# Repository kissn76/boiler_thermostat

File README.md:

# boiler_thermostat
Boiler theromstat based on ESP32

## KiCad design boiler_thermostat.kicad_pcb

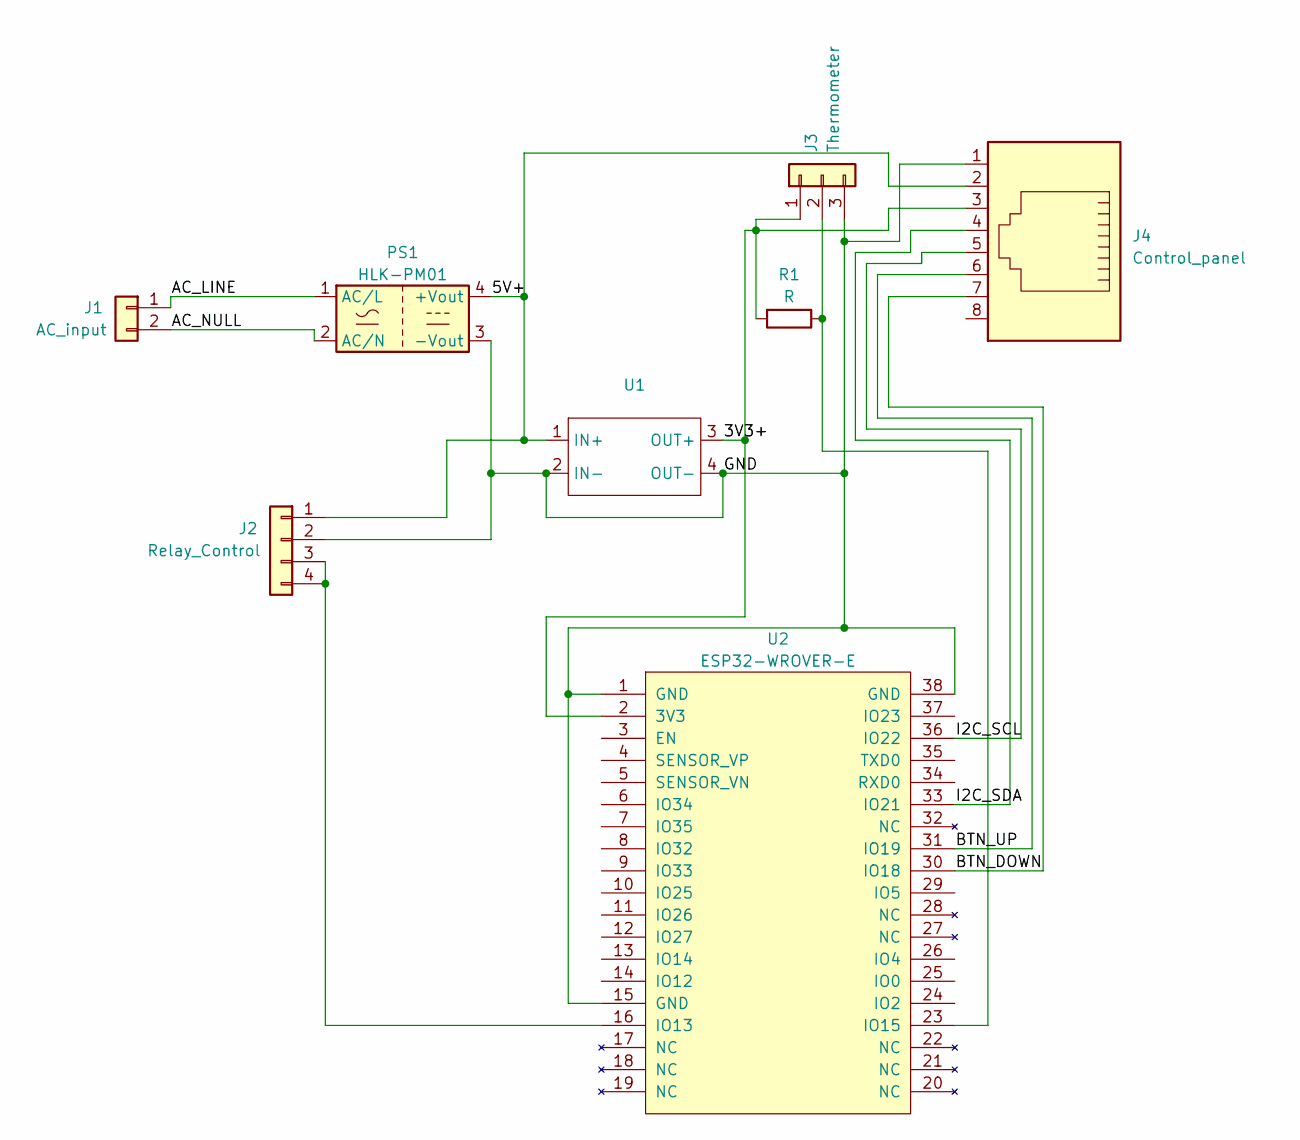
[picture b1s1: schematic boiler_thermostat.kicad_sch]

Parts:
J1: AC_input; Ninigi AC141R-02P-2.54
J2: Relay_Control; TerminalBlock_bornier-4_P5.08mm
J3: Thermometer; TerminalBlock_bornier-3_P5.08mm
J4: Control_panel; RJ45_Keystone_942
PS1: HLK-PM01; Converter_ACDC_HiLink_HLK-PMxx
R1: R; R_1206_3216Metric_Pad1.30x1.75mm_HandSolder
U1: DCDC_Mini560
U2: ESP32-WROVER-E; ESP32-WROVER-IE

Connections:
/3V3+: J3.1, J4.3, R1.2, U1.3 (OUT+), U2.2 (3V3)
/5V+: J2.1, J4.2, PS1.4 (+Vout), U1.1 (IN+)
/AC_LINE: J1.1, PS1.1 (AC/L)
/AC_NULL: J1.2, PS1.2 (AC/N)
/BTN_DOWN: J4.7, U2.30 (IO18)
/BTN_UP: J4.6, U2.31 (IO19)
/GND: J2.2, J3.3, J4.1, PS1.3 (-Vout), U1.2 (IN-), U1.4 (OUT-), U2.1 (GND), U2.15 (GND), U2.38 (GND)
/I2C_SCL: J4.5, U2.36 (IO22)
/I2C_SDA: J4.4, U2.33 (IO21)
unnamed: J2.3, J2.4, U2.16 (IO13)
unnamed: J3.2, R1.1, U2.23 (IO15)

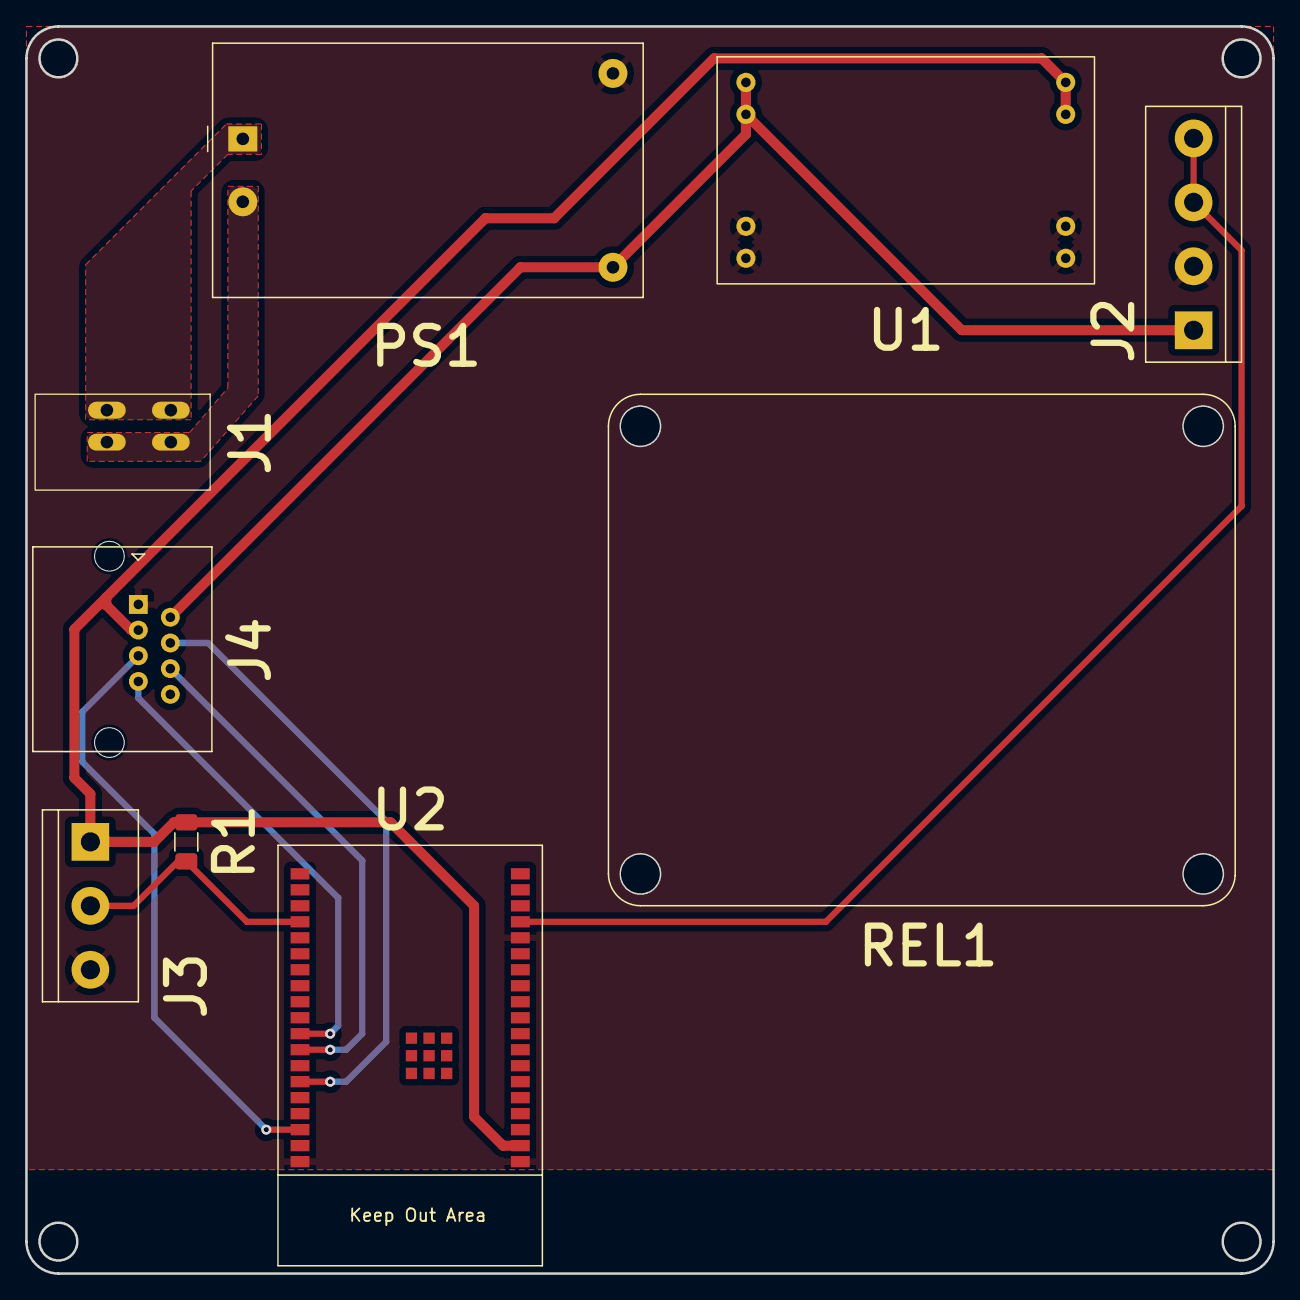
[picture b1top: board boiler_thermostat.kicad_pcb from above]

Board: 2 copper layers, 99.1 x 99.1 mm, 9 parts (0 on the bottom side), 11 nets.

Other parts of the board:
REL1: RELC-2CH-5V-UNI
